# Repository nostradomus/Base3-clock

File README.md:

# :clock10: µ-controller based Ternary clock with colorful read-out

## What

At school, kids learn to count from 1 to 10 (probably because of the number of fingers on your hands ;-). As such, in daily life, the decimal system is by far the most popular, and most intuitive to use. Computer scientists tend to prefer [binary](https://en.wikipedia.org/wiki/Binary_number) (0-1) or [hexadecimal](https://en.wikipedia.org/wiki/Hexadecimal) (x0-xF) systems. All of them are just a way of representing quantity (or whatever info you want) in a non-ambiguous way.

In a [ternary or base-3 systems](https://en.wikipedia.org/wiki/Ternary_numeral_system), only 0,1 and 2 are used. Being way less common, reading figures like 12201211 might make your brain-processor to get hot. The µ-controller driven clock in this repository is based on the ternary numeral system.

A web-version is already available in a [related repository](https://github.com/nostradomus/Base3-clock-webversion). In order to see a fully functional demo, click on [this link to our server](http://nostradomus.ddns.net/clock.html).

## Why

Some might find the idea a little crazy, others will say its fun. I think it is an excellent tool to train the brain... and I am probably having a twisted mind :laughing:

Anyhow, after having played around with javascript and css for the [web-version](https://github.com/nostradomus/Base3-clock-webversion), a new challenge popped up. I felt the need for a massive stand-alone living-room version.

## How

A first brainstorm session has resulted in a pretty complete [mindmap](docs/project-mindmap.mm) in the [docs folder](docs/).

Next, a breadboard prototype was build to test the feasibility of the concept. The LED's have been fit in an air-wire frame. Off-the-shelve modules (power supply, Arduino Nano and RTC) have been connected on a breadboard to develop the first version of the application. The LED colors have been carefully chosen by using the [analogue slider panel](https://github.com/nostradomus/LabTools_Analogue-input-slider-panel) from our **LabTools collection**.

After having finished the software development on the breadboard version, dedicated pcb's have been designed for the project :
- [RGB LED interface board](#rgb-led-interface-board)
- [µ-Controller board](#µ-controller-board)
- [stand-alone RTC module](#rtc-module) with square wave output option

The first pcb prototype has been assembled, to serve as a model for the final design of the [plexi lasercut-files](laser-cutting-files/) for the housing.

For the final version, an SMD-version has been designed, including several improvements. As nice-to-have feature, a sound-driven snooze function has been added.

## Progress status

 - [x] have a [crazy idea](#why)
 - [x] write the [functional specifications](#how)
 - [x] build an air-wire/breadboard [prototype](#how)
 - [x] design the final [electronics](#electronics)
 - [x] build a proof-of-concept for the final [electronics](#electronics)
 - [x] write [code for the µ-controller](#µ-controller-code) respecting best-practices
 - [ ] design and build a [state-of-the-art housing](#mechanical-construction)
 - [ ] write an [end-user manual](https://github.com/nostradomus/Base3-clock/wiki)

## Technical details

### How to read this clock

Each line or column (depending on how you mount the clock) represents a part of the time :

line | description | values
-----|-------------|-------
1 | hours | 00-23
2 | minutes | 00-59
3 | seconds | 00-59

Each element of the line represents one base-3 digit, with a different color for each possible value :
 - 0 : `light off`
 - 1 : `green`
 - 2 : `red`

In a horizontal configuration, the numbers should be read from right to left.

The rightmost element is the least significant trit (yes trit, not bit).

The leftmost element is the most significant trit.

### The Maths, a bit of theory...

The same way binary or decimal numeral systems are based on powers of their respective radices 2 and 10, the **ternary** system is based on powers of `3`.

trit    | least significant |       |        |         |          | ... | most significant
--------|-------------------|-------|--------|---------|----------|-----|-----------------
power   | 0                 | 1     | 2      | 3       | 4        | ... |
decimal | 1                 | 3     | 9      | 27      | 81       | ... |
range   | 0/1/2             | 0/3/6 | 0/9/18 | 0/27/54 | 0/81/162 | ... |

So to convert a ternary number to the decimal system, you have to start with the rightmost digit, multiply it with 3^0, multiply the next digit with 3^1, 3^2, and so on...

So for example (11021)ter = 1x3^0 + 2x3^1 + 0x3^2 + 1x3^3 + 1x3^4 =  (111)dec

The ternary numbers for the clock will have maximum 4 digits (max 3 for the hours).
 - `hours` : (000)ter - (222)ter => (0)dec - (26)dec
 - `mins/secs` : (0000)ter - (2222)ter => (0)dec - (80)dec

### Electronics

#### RTC module

One of the key components to build a clock is a basic RTC circuit. This piece of hardware will give you the correct time, and continue counting every second. A crystal driven oscillator will do this with minimum drift. Next, as you don't want to set the clock after every power cut (or after having it switched off for a while), we'll connect a small battery to the chip, to remember our settings, and to continue counting. For this clock I have chosen the [DS1307](pdf-files/datasheet-DS1307.pdf) from Maxim Integrated. The circuit is based on the specifications in the [manufacturer's datasheet](pdf-files/datasheet-DS1307.pdf). All communications with the chip will be over I2C. The only tricky part with this hardware is the [PCB layout](images/RTC-board-pcb.png) around the crystal and chip's oscillator section. No signal lines should cross these zones, unless protected by a ground plane in between.

#### RGB LED interface board

For the first version of this clock, I have opted for intelligent RGB-LED's as interface. It concerns [WS2812b](pdf-files/datasheet-WS2812B.pdf) LED's which need power and serial data. Each LED is having four connections (+5V, GND, data in, and data out). The µ-controller has to send all data as a long train of bits over only one datapin. Each LED, with its small built-in chip, will strip-off the first frame from data train on its data "in" pin, and transparently push forward all other frames on its data "out" pin. The µ-controller will, as such, produce twelve dataframes for each interface refresh. The twelve LED's, installed in three rows of four, are each having a specific function. The [LED pcb board](images/LED-board-pcb.png) has been designed as single layer. However the [WS2812b](pdf-files/datasheet-WS2812B.pdf) LED's being SMD components, the copper layer has been designed on the component side of the pcb. Depending on the mechanical requirements of your housing, the through-hole components can be mounted on either side of this pcb. It might however be a good idea to bend the capacitors lead 90° in case of mounting on the component side, to limit the overall height.

LED | c1         | c2       | c3       | c4
----|------------|----------|----------|-----------
r1  | mode       | hour mst | <......> | hour lst
r2  | minute mst | <....... | .......> | minute lst
r3  | second mst | <....... | .......> | second lst

#### µ-Controller board

The brain of the system is based on an [ATmega328p](pdf-files/datasheet-ATmega328P.pdf) µ-controller (yes, like the [Arduino UNO](https://www.arduino.cc/)). The choice was pretty obvious for multiple reasons. The design is easy, the IDE is well-known, specific libraries exist for the RTC and RGB LED's, and a hardware interface is available for the I2C protocol. The designed configuration is rather straightforward as well. Around IC2, some standard circuitry can be found. X2, C4 and C5 provide a stable clock for the controller. Reseting the running application can be done by button S1 (and R1). This will however not affect the clock time (stored in the RTC chip), or the alarm settings (stored in the ATmega's EEPROM). L1 and C2 provide noise canceling for the ADC's, which we will use for the dusk detection (LDR1 and R5 voltage divider), and the optional [color calibration module](https://github.com/nostradomus/LabTools_Analogue-input-slider-panel) (CON4). Connector SER1 can be used with any serial-to-usb converter, to visualize the output during color calibration (RX and TX lines). CON3 is a so called in-system-programming connector to update the application without having to extract the [ATmega328p](pdf-files/datasheet-ATmega328P.pdf) µ-controller. The whole system is powered by a standard USB power supply, to be connected to the micro-USB connector CON2. Optionaly, R1 and LED1 can be fit on the pcb as a power-ON indicator. Diode D1 protects the electronics against misconnection of the power supply. As a simplified keyboard, S2 and S3 will get 'mode' and 'set' functionality. The required pull-up resistors are integrated in the controller, and set by software. The same applies for the snooze button on CON5. IC1, X1, C1 and BAT1 represent the RTC part of the clock as described [above](#rtc-module). The two pull-up resistors R3 and R4 are needed for stable I2C communication between the µ-controller and the RTC chip.

### µ-Controller code

The software has been written in the free [Arduino IDE](https://www.arduino.cc/en/Main/Software), or as [sourcecode](https://github.com/arduino/Arduino/). Two specific libraries are required to integrate the [DS1307 RTC module](https://github.com/adafruit/RTClib), and the [neopixel LED's](https://github.com/adafruit/Adafruit_NeoPixel).

As the application has been written as an Arduino sketch, there are various ways to load the code in the controller. In below picture, I used the ICSP connector on the µ-controller board in combination with my [programming shield](https://github.com/nostradomus/ATtinyISPprogrammerShield). Instructions on how to proceed can be found in [this repository](https://github.com/nostradomus/ATtinyISPprogrammerShield). A basic serial-to-USB adapter has been connected to debug the application. You can use your favorite serial console software, or use the [python script](tools/SerialMonitor.py) included in the [tools folder](tools/) of this project.

So far, three versions of the firmware are available in the [source folder](source/) :

version | name                                                                                  | description
--------|---------------------------------------------------------------------------------------|----------------------------------------------------------
v1.0a   | [ternary_clock_rainbow_alarm.ino](source/ternary_clock_rainbow_alarm.ino)             | base version with mood-light alarm animation
v1.0b   | [ternary_clock_twinklingstar_alarm.ino](source/ternary_clock_twinklingstar_alarm.ino) | base version with mutant LED alarm animation
v1.1    | [ternary_clock.ino](source/ternary_clock.ino)                                         | latest release with selector function for alarm animation

### Mechanical construction

The housing consists of several layers of lasercut and engraved plexi plates (3 & 6mm). The required files to cut out these plexi sheets are available both in [.cdr or CorelDraw format](laser-cutting-files/) or in [pdf format](pdf-files/). A legend on which color to use for which action (contour cutting, inside cut-outs, engraving) is available as an instruction in the [readme document](laser-cutting-files/README.md) which is accompanying the files.

### Building instructions

`...on the way...`

## Contributors

If you are having any good suggestions, just drop me a line [:email:](http://nostradomus.ddns.net/contactform.html).
If feasible, I'll be happy to implement proposed improvements.
And if you are having lots of time, I'll be happy to share the work with you ;-).

When you create your own version, don't forget to send us some nice pictures of your construction. We'll be happy to publish them in the :confetti_ball:Hall of Fame:confetti_ball:.

## :globe_with_meridians: License

At this moment, there is no specific license attached to this project.

So, today, if you like it, have fun with it (at your own risk of course :-D), and especially, be creative.

Oh, and when using anything from this repository, it is highly appreciated if you mention its origin.

If you would like to use any of this work (or the whole project) for commercial use, first [contact us :email:](http://nostradomus.ddns.net/contactform.html), so we can add the appropriate license, which best fits your business.

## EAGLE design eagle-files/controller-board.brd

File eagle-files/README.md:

This folder contains all files required to open the project in the EAGLE PCB software [(download here)](http://www.autodesk.com/products/eagle/free-download) :

 - .sch : schematic file
 - .brd : pcb layout file

 These files should (grouped in a folder) either be copied in Eagle's project directory (see below image of the settings window). The Eagle directory settings also accept multiple paths. The Eagle syntax requires columns as path separators.

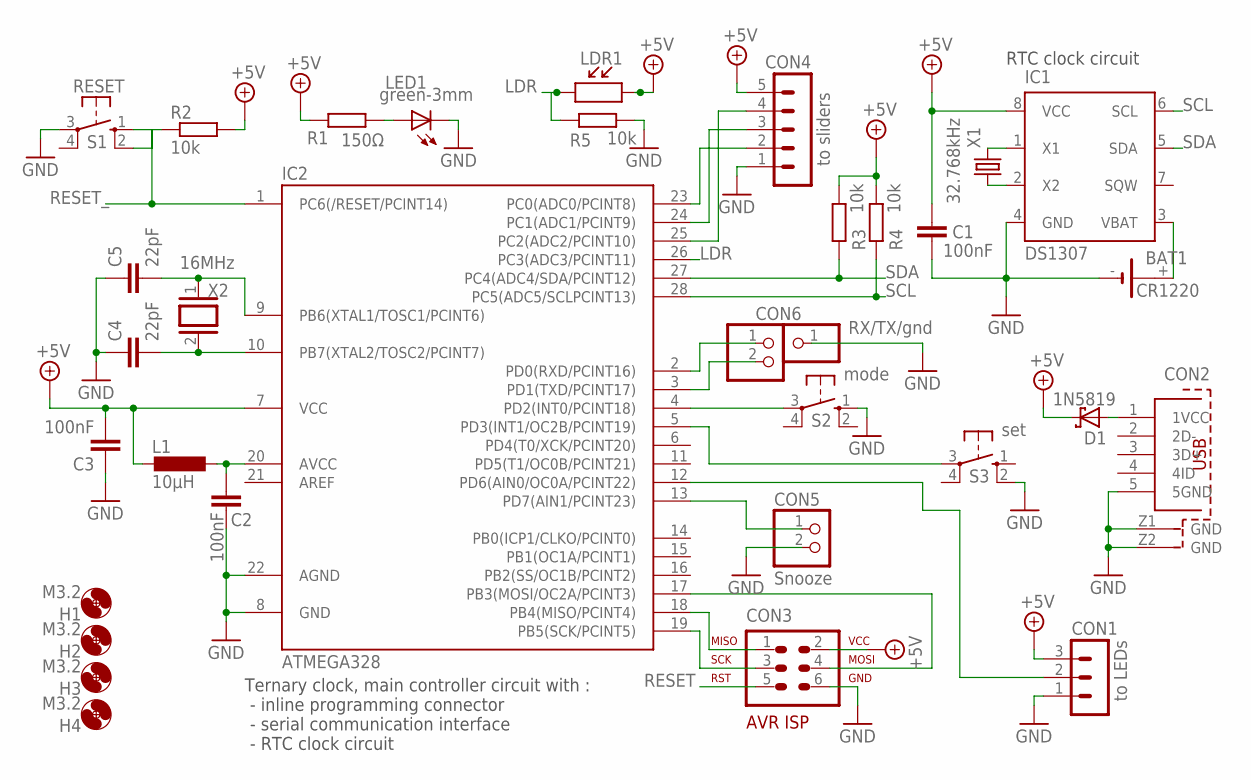
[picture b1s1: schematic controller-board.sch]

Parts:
BAT1: CR1220; CR1220HOLDER
C1, C2, C3: 100nF; C050-025X075
C4, C5: 22pF; C2.5-2
CON1: to LEDs; MA03-1
CON2: 614105150721
CON3: AVR-ISP; AVR-ISP-6
CON4: to sliders; MA05-1
CON5: Snooze; 1X02
CON6: RX/TX/gnd; 1X02
CON6B: Ser-GND; 1X01
D1: 1N5819; DO41-7.6
H1, H2, H3, H4: M3.2; 3,2
IC1: DS1307; DIL08
IC2: ATMEGA328; DIL28-3
L1: 10µH; 0207/7
LDR1: LDR
LED1: green-3mm; LED3MM
R1: 150Ω; 0207/7
R2, R3, R4, R5: 10k; 0207/7
S1: RESET; B3F-10XX
S2: mode; B3F-10XX
S3: set; B3F-10XX
X1: 32.768kHz; TC38H
X2: 16MHz; QS

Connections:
+5V: C1.1, C3.2, CON1.3, CON3.2, CON4.5, D1.C, IC1.8 (VCC), IC2.7 (VCC), L1.2, LDR1.P$2, R1.2, R2.2, R3.2, R4.2
GND: BAT1.-, C1.2, C2.1, C3.1, C4.1, C5.1, CON1.1, CON2.5 (5GND), CON2.Z1 (GND), CON2.Z2 (GND), CON3.6, CON4.1, CON5.2, CON6B.1, IC1.4 (GND), IC2.8 (GND), IC2.22 (AGND), LED1.K (C), R5.2, S1.3, S2.1 (S), S3.2 (S1)
LDR: IC2.26 (PC3(ADC3/PCINT11)), LDR1.P$1, R5.1
unnamed: C5.2, IC2.9 (PB6(XTAL1/TOSC1/PCINT6)), X2.1
unnamed: C2.2, IC2.20 (AVCC), L1.1
unnamed: IC2.4 (PD2(INT0/PCINT18)), S2.3
unnamed: IC2.5 (PD3(INT1/OC2B/PCINT19)), S3.3
unnamed: CON1.2, IC2.12 (PD6(AIN0/OC0A/PCINT22))
unnamed: C4.2, IC2.10 (PB7(XTAL2/TOSC2/PCINT7)), X2.2
unnamed: CON3.4, IC2.17 (PB3(MOSI/OC2A/PCINT3))
unnamed: CON3.1, IC2.18 (PB4(MISO/PCINT4))
unnamed: CON3.3, IC2.19 (PB5(SCK/PCINT5))
unnamed: CON6.2, IC2.3 (PD1(TXD/PCINT17))
unnamed: CON6.1, IC2.2 (PD0(RXD/PCINT16))
unnamed: CON4.4, IC2.25 (PC2(ADC2/PCINT10))
unnamed: CON4.3, IC2.24 (PC1(ADC1/PCINT9))
unnamed: CON4.2, IC2.23 (PC0(ADC0/PCINT8))
unnamed: IC1.1 (X1), X1.2
unnamed: IC1.2 (X2), X1.1
unnamed: BAT1.+, IC1.3 (VBAT)
unnamed: CON5.1, IC2.13 (PD7(AIN1/PCINT23))
unnamed: CON2.1 (1VCC), D1.A
unnamed: LED1.A, R1.1
RESET: CON3.5, R2.1, S1.2 (S1)
RESET_: IC2.1 (PC6(/RESET/PCINT14)), S1.1 (S)
SCL: IC1.6 (SCL), IC2.28 (PC5(ADC5/SCLPCINT13)), R4.1
SDA: IC1.5 (SDA), IC2.27 (PC4(ADC4/SDA/PCINT12)), R3.1

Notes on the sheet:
RTC clock circuit
Ternary clock, main controller circuit with : - inline programming connector - serial communication interface - RTC clock circuit

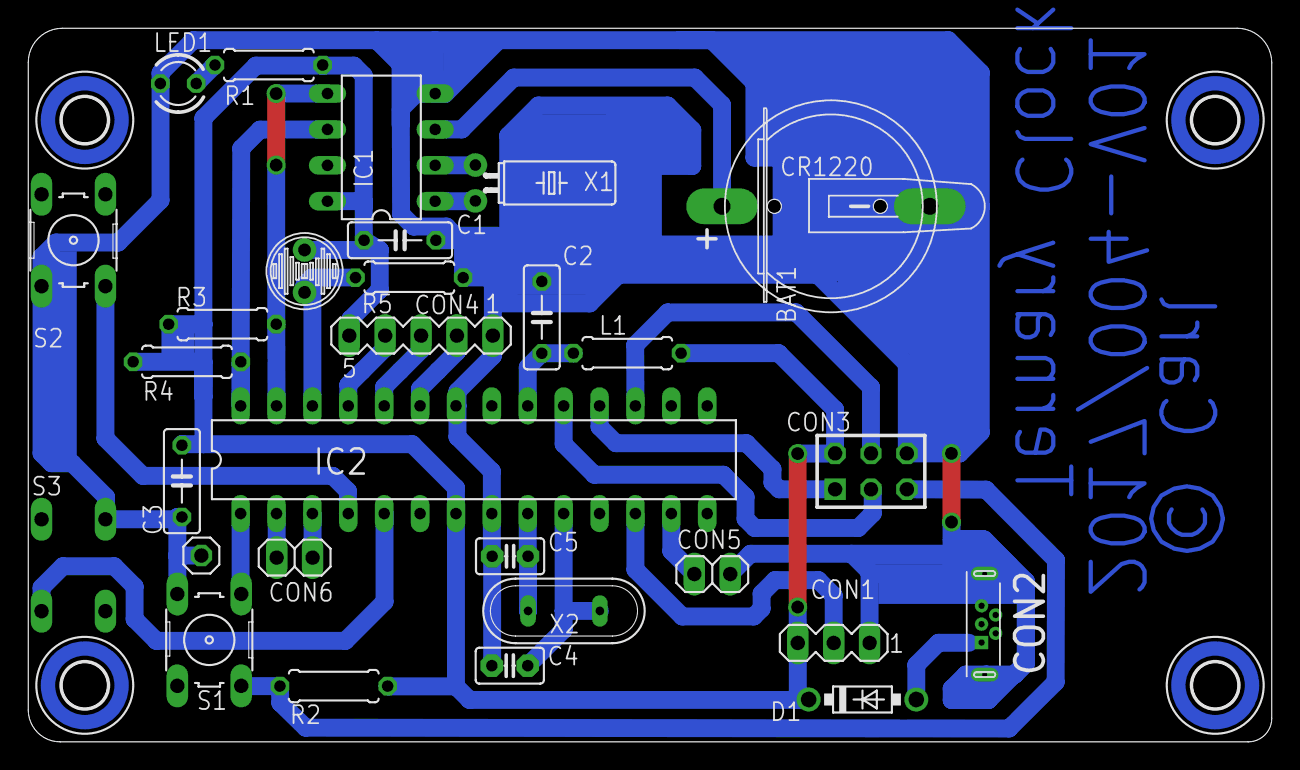
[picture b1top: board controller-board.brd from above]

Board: 2 copper layers, 87.9 x 50.4 mm, 33 parts (1 on the bottom side), 27 nets.

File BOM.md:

### BOM - bill of materials

#### µ-controller board

Part     | Value          | Package      | Description  
-------- | -------------- | ------------ | ---------------------------------------------------------                            
R1       | 2.2kΩ          | 0207/7       | resistor                                            
R2,3,4,5 | 10kΩ           | 0207/7       | resistor                                            
LDR1     | [PGM5537](/pdf-files/datasheet-LDR-pgm5537.pdf)        | 0604/4       | light dependent resistor                                           
C1,2,3   | 100nF          | C050-025X075 | capacitor                                           
C4,5     | 22pF           | C2.5-2       | capacitor                                 
L1       | 10µH           | 0207/7       | inductor                                            
D1       | 1N5819         | DO41-7.6     | resistor                                            
LED1     | 3mm green      | 3mm          | LED                        
X1       | 32.768kHz      | TC38H        | RTC clock crystal                                            
X2       | 16MHz          | QS           | CPU clock crystal                                            
IC1      | [DS1307+](/pdf-files/datasheet-DS1307.pdf)        | DIL08        | I2C-Bus CLOCK/CALENDAR                                                            
IC2      | [ATmega328p](/pdf-files/datasheet-ATmega328P.pdf)     | DIL28        | ATmega328p µ-controller             
IC1b     | 8-pin          | DIL08        | IC socket                                                            
IC2b     | 28-pin         | DIL28        | IC socket                                                                     
BAT1     | CR1220         | CR1220       | through-hole battery holder (CR1220)
BAT1b    | CR1220-3V      | CR1220       | 3 volt lithium battery
CON1     | 3-pin          | SIL03        | pin header to connect the µ-controller and LED boards
CON2     | vertical µUSB  | µUSB-V-B     | vertical micro USB connector (type B) with power pins only
CON3     | 2x3 pin-header | 2x3          | ICSP, AVR ISP-6 Serial Programming Header (optional)
CON4     | 5-pin          | SIL05        | pin header to connect the analogue slider board (optional)
CON5     | 2-pin          | SIL02        | pin header to connect the snooze button
CON6     | 2-pin          | SIL02        | pin header to connect RX and TX for the serial communication
CON6b    | 1-pin          | SIL01        | pin header to connect the GND for the serial communication
S1       | momentary      | 6x6x6mm      | momentary tact push button, button shaft length 6mm                        
S2,3     | momentary      | 6x6x16mm     | momentary tact push button, button shaft length 16mm                        
S2b,3b   | cap            | 6x6          | tact push button caps (white)                        

#### LED-board-pcb

Part | Value | Package | Description  
---- | ----- | ------- | -----------

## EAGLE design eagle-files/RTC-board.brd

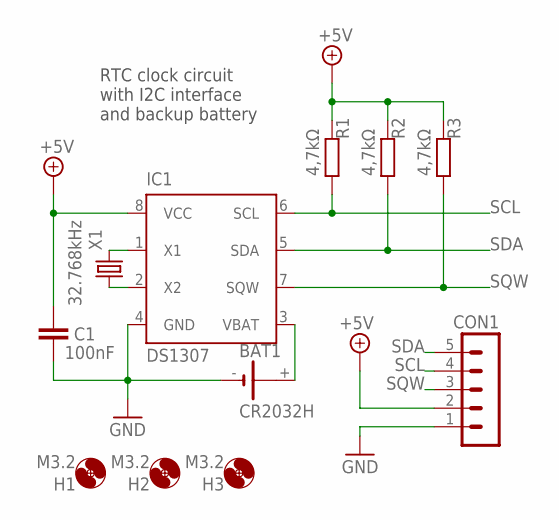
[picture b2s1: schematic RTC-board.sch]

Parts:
BAT1: CR2032H
C1: 100nF; C050-025X075
CON1: MA05-1
H1, H2, H3: M3.2; 3,2
IC1: DS1307; DIL08
R1, R2, R3: 4,7kΩ; 0207/7
X1: 32.768kHz; TC38H

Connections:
+5V: C1.1, CON1.2, IC1.8 (VCC), R1.2, R2.2, R3.2
GND: BAT1.-, C1.2, CON1.1, IC1.4 (GND)
unnamed: IC1.1 (X1), X1.2
unnamed: IC1.2 (X2), X1.1
unnamed: BAT1.+, IC1.3 (VBAT)
SCL: CON1.4, IC1.6 (SCL), R1.1
SDA: CON1.5, IC1.5 (SDA), R2.1
SQW: CON1.3, IC1.7 (SQW), R3.1

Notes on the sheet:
RTC clock circuit with I2C interface and backup battery

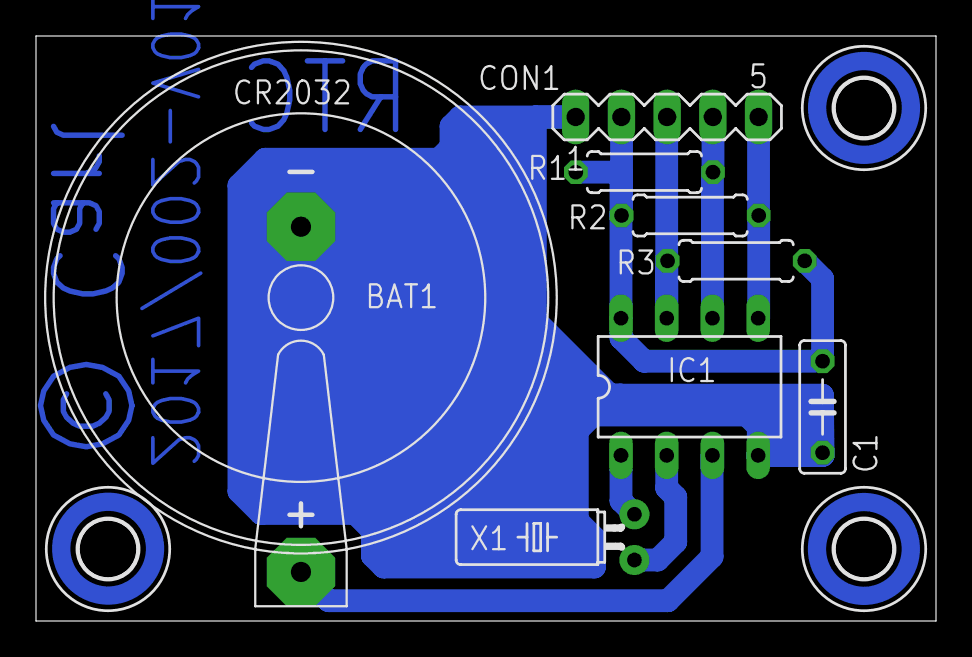
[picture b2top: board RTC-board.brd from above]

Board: 2 copper layers, 50.0 x 32.5 mm, 11 parts (0 on the bottom side), 8 nets.

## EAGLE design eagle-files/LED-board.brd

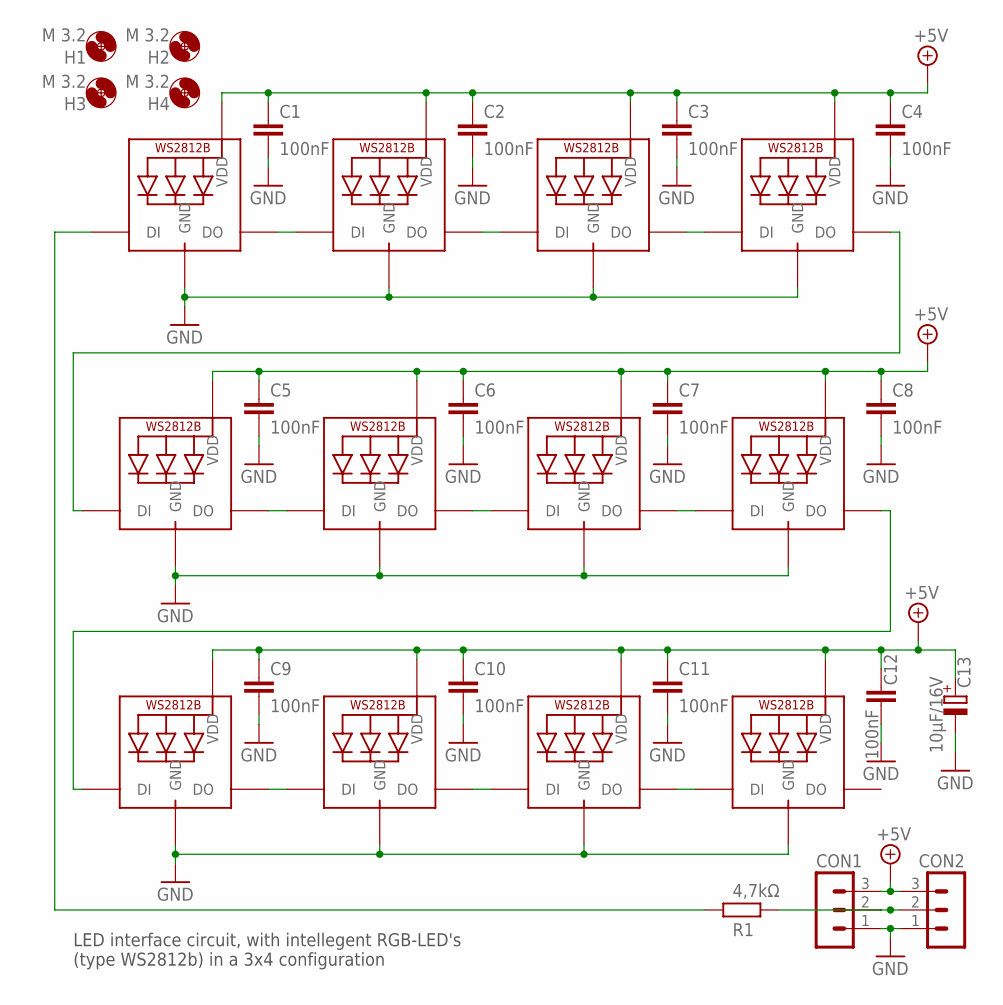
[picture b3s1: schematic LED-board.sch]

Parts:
C1, C2, C3, C4, C5, C6, C7, C8, C9, C10, C11, C12: 100nF; C050-025X075
C13: 10µF/16V; E2-5
CON1, CON2: MA03-1
H1, H2, H3, H4: M 3.2; 3,2
LED1, LED2, LED3, LED4, LED5, LED6, LED7, LED8, LED9, LED10, LED11, LED12: WS2812B5050; WS2812B
R1: 4,7kΩ; 0207/7

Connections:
+5V: C1.1, C2.1, C3.1, C4.1, C5.1, C6.1, C7.1, C8.1, C9.1, C10.1, C11.1, C12.1, C13.+, CON1.3, CON2.3, LED1.1-VDD (VDD), LED2.1-VDD (VDD), LED3.1-VDD (VDD), LED4.1-VDD (VDD), LED5.1-VDD (VDD), LED6.1-VDD (VDD), LED7.1-VDD (VDD), LED8.1-VDD (VDD), LED9.1-VDD (VDD), LED10.1-VDD (VDD), LED11.1-VDD (VDD), LED12.1-VDD (VDD)
GND: C1.2, C2.2, C3.2, C4.2, C5.2, C6.2, C7.2, C8.2, C9.2, C10.2, C11.2, C12.2, C13.-, CON1.1, CON2.1, LED1.3-GND (GND), LED2.3-GND (GND), LED3.3-GND (GND), LED4.3-GND (GND), LED5.3-GND (GND), LED6.3-GND (GND), LED7.3-GND (GND), LED8.3-GND (GND), LED9.3-GND (GND), LED10.3-GND (GND), LED11.3-GND (GND), LED12.3-GND (GND)
unnamed: CON1.2, CON2.2, R1.2
unnamed: LED1.2-DOUT (DO), LED2.4-DIN (DI)
unnamed: LED2.2-DOUT (DO), LED3.4-DIN (DI)
unnamed: LED3.2-DOUT (DO), LED4.4-DIN (DI)
unnamed: LED1.4-DIN (DI), R1.1
unnamed: LED5.2-DOUT (DO), LED6.4-DIN (DI)
unnamed: LED6.2-DOUT (DO), LED7.4-DIN (DI)
unnamed: LED7.2-DOUT (DO), LED8.4-DIN (DI)
unnamed: LED8.2-DOUT (DO), LED9.4-DIN (DI)
unnamed: LED9.2-DOUT (DO), LED10.4-DIN (DI)
unnamed: LED10.2-DOUT (DO), LED11.4-DIN (DI)
unnamed: LED11.2-DOUT (DO), LED12.4-DIN (DI)
unnamed: LED4.2-DOUT (DO), LED5.4-DIN (DI)

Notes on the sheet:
LED interface circuit, with intellegent RGB-LED's (type WS2812b) in a 3x4 configuration

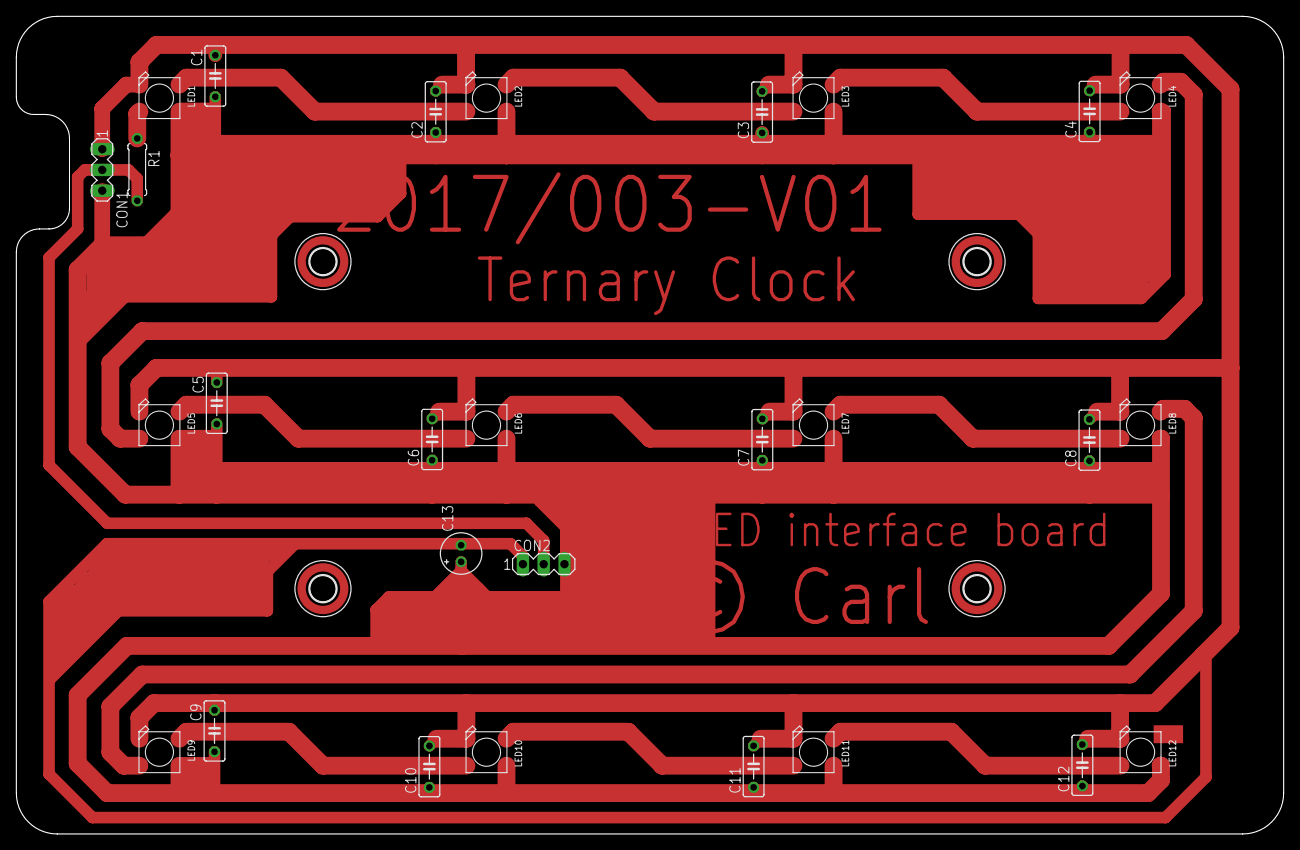
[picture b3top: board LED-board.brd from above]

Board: 2 copper layers, 155.0 x 100.0 mm, 32 parts (0 on the bottom side), 15 nets.

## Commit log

2017-04-28 Rename project mindmap.mm to project-mindmap.mm
2017-06-07 pcb layout optimizations
    - micro USB connector replaced with power-only version
    - mechanical protection added for the RTC oscillator
    - position GND pin for serial output optimized
    - improved position for through-hole version of the battery holder
2017-06-07 pub layout optimizations
    - micro USB connector replaced with power-only version
    - mechanical protection added for the RTC oscillator
    - position GND pin for serial output optimized
    - improved position for through-hole version of the battery holder

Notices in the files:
eagle-files/LED-board.brd:
© Carl
parts and their libraries:
Wurth_Elektronik_Electromechanic_Input-O: Copyright: Würth Elektronik
